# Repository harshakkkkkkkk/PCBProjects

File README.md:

# 🔹 PCB Design Projects

---

## 🔹 List of projects available in this repository  
1. IR Proximity Sensor

---

## 🔹 Author

**Name:** Harshak V P  
**LinkedIn:** [linkedin.com/in/harshakvp](https://www.linkedin.com/in/harshakvp/)

This project was developed as a learning exercise in PCB Design.  
Feel free to use, modify, and extend it as needed!

---

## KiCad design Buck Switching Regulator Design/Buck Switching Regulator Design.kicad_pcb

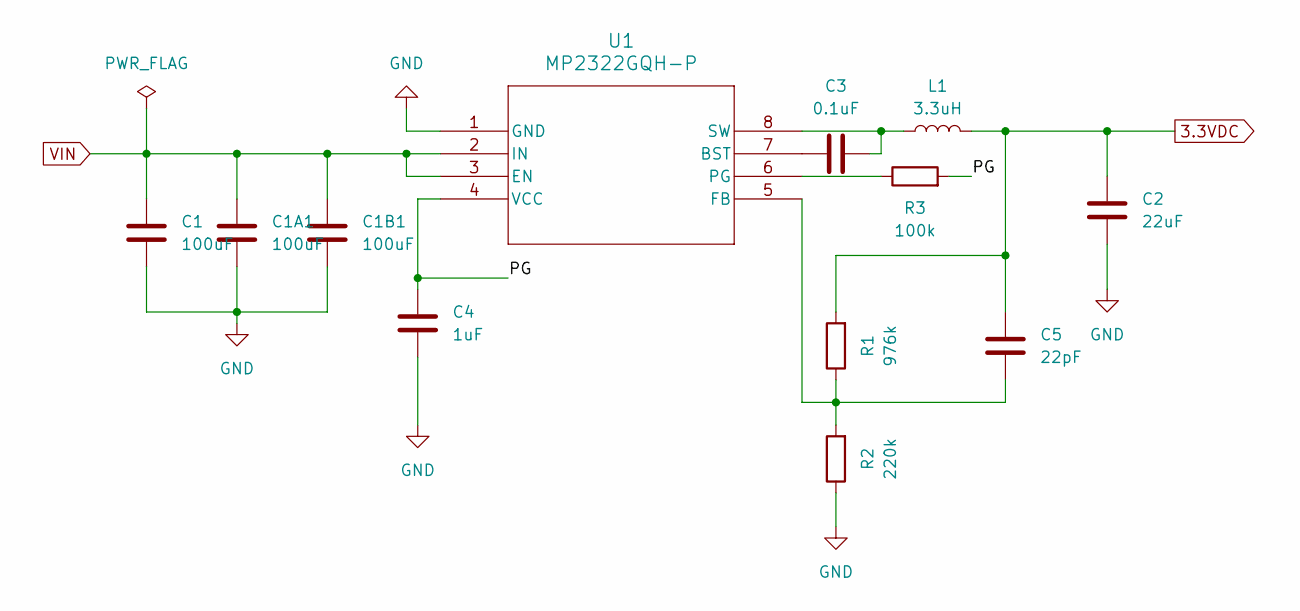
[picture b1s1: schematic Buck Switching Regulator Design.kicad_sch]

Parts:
C1, C1A1, C1B1: 100uF; C_0603_1608Metric
C2: 22uF; C_1206_3216Metric
C3: 0.1uF; C_0603_1608Metric
C4: 1uF; C_0603_1608Metric
C5: 22pF; C_0603_1608Metric
L1: 3.3uH; L_Walsin_WLFM252009x
R1: 976k; R_0603_1608Metric
R2: 220k; R_0603_1608Metric
R3: 100k; R_0603_1608Metric
U1: MP2322GQH-P; QFN-8_1p5MMx2MM_MNP

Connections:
3.3VDC: C2.2, C5.2, L1.2, R1.2
/PG: C4.1, R3.2, U1.4 (VCC)
GND: C1.2, C1A1.2, C1B1.2, C2.1, C4.2, R2.1, U1.1 (GND)
unnamed: C3.1, U1.7 (BST)
unnamed: C5.1, R1.1, R2.2, U1.5 (FB)
unnamed: R3.1, U1.6 (PG)
unnamed: C3.2, L1.1, U1.8 (SW)
VIN: C1.1, C1A1.1, C1B1.1, U1.2 (IN), U1.3 (EN)

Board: 2 copper layers, 12 parts (0 on the bottom side), 8 nets, no tracks yet.

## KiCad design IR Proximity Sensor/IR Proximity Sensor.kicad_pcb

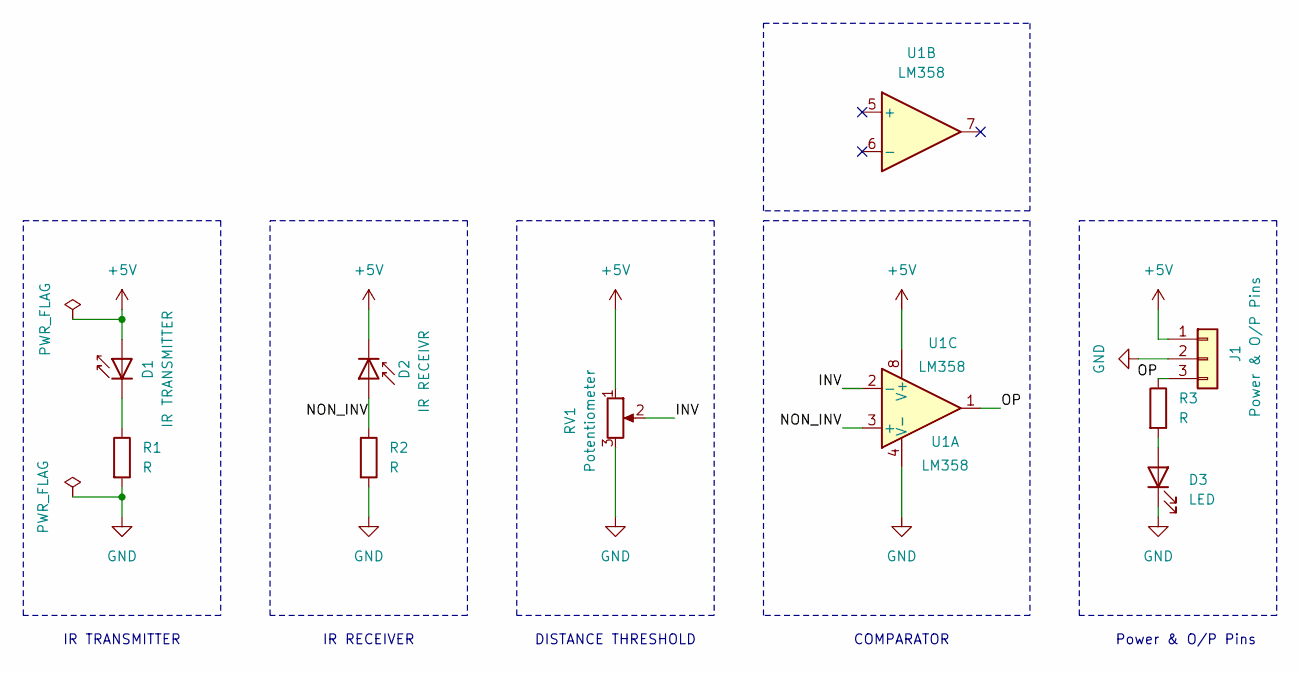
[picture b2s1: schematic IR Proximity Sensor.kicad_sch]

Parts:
D1: IR TRANSMITTER; LED_D3.0mm_IRBlack
D2: IR RECEIVR; LED_D3.0mm
D3: LED; LED_D3.0mm
J1: Power & O/P Pins; PinSocket_1x03_P2.54mm_Horizontal
R1, R2, R3: R; R_Axial_DIN0207_L6.3mm_D2.5mm_P7.62mm_Horizontal
RV1: Potentiometer; Potentiometer_ACP_CA6-VSMD_Vertical
U1: LM358; DIP-8_W7.62mm

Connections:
+5V: D1.2 (A), D2.1 (K), J1.1, RV1.1, U1.8 (V+)
/INV: RV1.2, U1.2 (-)
/NON_INV: D2.2 (A), R2.1, U1.3 (+)
/OP: J1.3, R3.1, U1.1
GND: D3.1 (K), J1.2, R1.2, R2.2, RV1.3, U1.4 (V-)
unnamed: D1.1 (K), R1.1
unnamed: D3.2 (A), R3.2

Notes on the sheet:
DISTANCE THRESHOLD
COMPARATOR
IR TRANSMITTER
IR RECEIVER
Power & O/P Pins

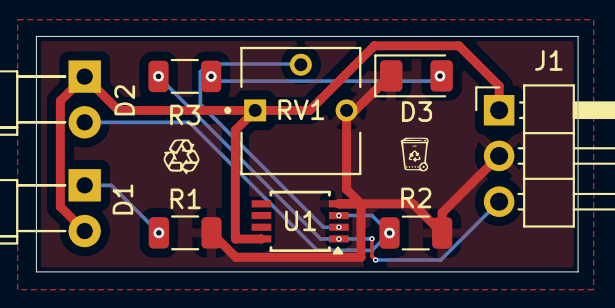
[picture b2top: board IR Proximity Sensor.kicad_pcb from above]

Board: 2 copper layers, 30.1 x 13.1 mm, 9 parts (0 on the bottom side), 7 nets.

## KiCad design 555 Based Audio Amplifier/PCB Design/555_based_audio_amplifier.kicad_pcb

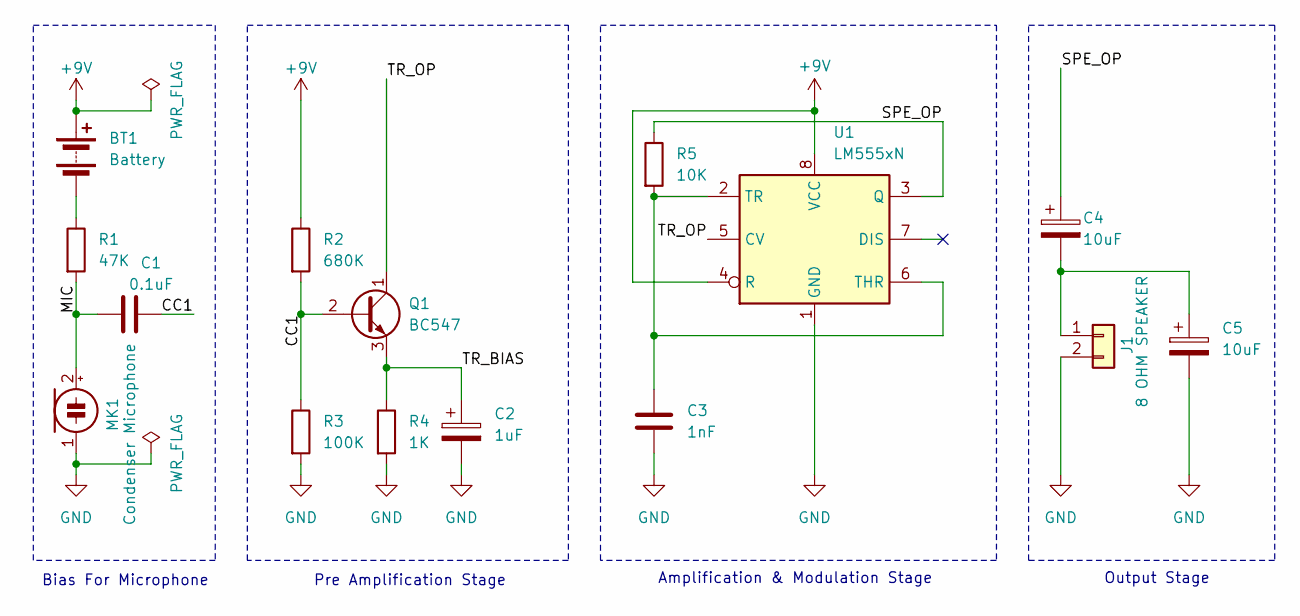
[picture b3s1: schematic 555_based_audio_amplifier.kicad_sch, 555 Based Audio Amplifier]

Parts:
BT1: Battery; PinHeader_1x02_P2.54mm_Vertical
C1: 0.1uF; C_Disc_D3.0mm_W1.6mm_P2.50mm
C2: 1uF; C_Disc_D3.0mm_W1.6mm_P2.50mm
C3: 1nF; C_Disc_D3.0mm_W1.6mm_P2.50mm
C4, C5: 10uF; CP_Radial_D5.0mm_P2.50mm
J1: 8 OHM SPEAKER; PinHeader_1x02_P2.54mm_Vertical
MK1: Condenser Microphone; PinHeader_1x02_P2.54mm_Vertical
Q1: BC547; TO-92_Inline
R1: 47K; R_Axial_DIN0207_L6.3mm_D2.5mm_P7.62mm_Horizontal
R2: 680K; R_Axial_DIN0207_L6.3mm_D2.5mm_P7.62mm_Horizontal
R3: 100K; R_Axial_DIN0207_L6.3mm_D2.5mm_P7.62mm_Horizontal
R4: 1K; R_Axial_DIN0207_L6.3mm_D2.5mm_P7.62mm_Horizontal
R5: 10K; R_Axial_DIN0207_L6.3mm_D2.5mm_P7.62mm_Horizontal
U1: LM555xN; DIP-8_W7.62mm

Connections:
+9V: BT1.1 (+), R2.1, U1.4 (R), U1.8 (VCC)
/CC1: C1.2, Q1.2 (B), R2.2, R3.1
/MIC: C1.1, MK1.2 (+), R1.2
/SPE_OP: C4.1, R5.1, U1.3 (Q)
/TR_BIAS: C2.1, Q1.3 (E), R4.1
/TR_OP: Q1.1 (C), U1.5 (CV)
GND: C2.2, C3.1, C5.2, J1.2, MK1.1 (-), R3.2, R4.2, U1.1 (GND)
unnamed: BT1.2 (-), R1.1
unnamed: C4.2, C5.1, J1.1
unnamed: C3.2, R5.2, U1.2 (TR), U1.6 (THR)

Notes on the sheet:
Output Stage
Bias For Microphone
Amplification & Modulation Stage
Pre Amplification Stage

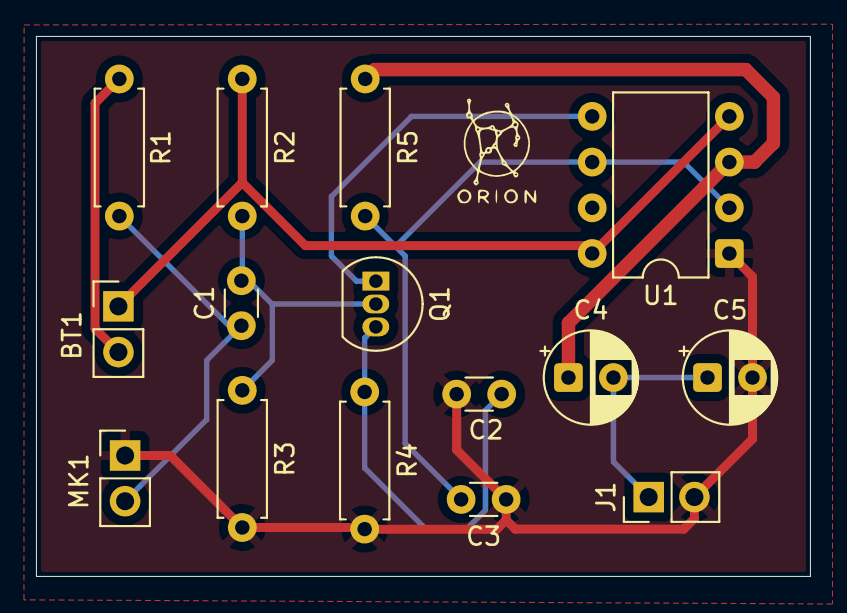
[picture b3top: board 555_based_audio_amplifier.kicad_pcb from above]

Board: 2 copper layers, 43.0 x 30.0 mm, 15 parts (0 on the bottom side), 10 nets.

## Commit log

2025-06-01 Initial commit, commited all the files to the repository
2025-06-01 Commited updated directory
2025-06-01 First commit: adding files to the repository
2025-06-02 Done with PCB routing and zone filling
2025-06-19 Deleted a project
2025-06-19 Deleted 555 Based Audio Amplifier
2025-06-19 Updated footprints and PCB layout
2025-06-19 All new changes commited
2025-07-19 Added 3D model to the potentiometer
2025-08-03 Schematics v1.0
2025-08-03 Updated the .gitignore file
2025-08-04 Updated Footprints
2025-08-04 PCB Layout: Components Placed
